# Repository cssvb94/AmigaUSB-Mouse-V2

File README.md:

# Amiga USB Mouse V2

USB to Amiga mouse interface using Arduino Pro Mini 3.3V and USB Host Shield Mini

USB Host Mini and Arduino Pro Mini mounting:

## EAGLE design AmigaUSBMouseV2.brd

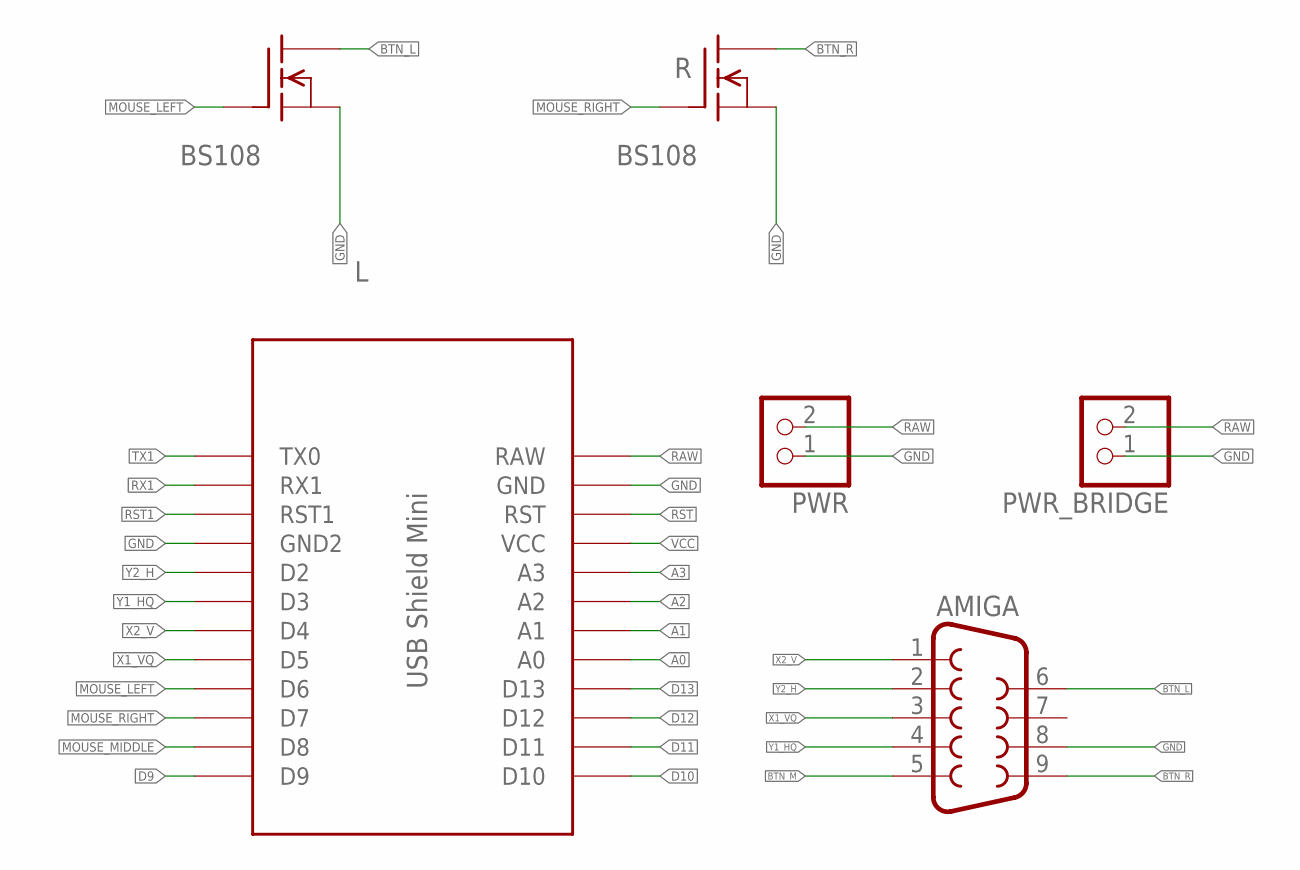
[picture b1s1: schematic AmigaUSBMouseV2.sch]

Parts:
AMIGA: F09D
L: BS108; TO92-INLINE
PWR: PINHD-1X2; 1X02
PWR_BRIDGE: PINHD-1X2; 1X02
R: BS108; TO92-INLINE
U$2: USB-SHIELD-MINI

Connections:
A0: U$2.A0
A1: U$2.A1
A2: U$2.A2
A3: U$2.A3
BTN_L: AMIGA.6, L.1 (D)
BTN_M: AMIGA.5
BTN_R: AMIGA.9, R.1 (D)
D9: U$2.D9
D10: U$2.D10
D11: U$2.D11
D12: U$2.D12
D13: U$2.D13
GND: AMIGA.8, L.3 (S), PWR.1, PWR_BRIDGE.1, R.3 (S), U$2.GND, U$2.GND1 (GND2)
MOUSE_LEFT: L.2 (G), U$2.D6
MOUSE_MIDDLE: U$2.D8
MOUSE_RIGHT: R.2 (G), U$2.D7
RAW: PWR.2, PWR_BRIDGE.2, U$2.RAW
RST: U$2.RST
RST1: U$2.RST1
RX1: U$2.RX1
TX1: U$2.TX0
VCC: U$2.VCC
X1_VQ: AMIGA.3, U$2.D5
X2_V: AMIGA.1, U$2.D4
Y1_HQ: AMIGA.4, U$2.D3
Y2_H: AMIGA.2, U$2.D2

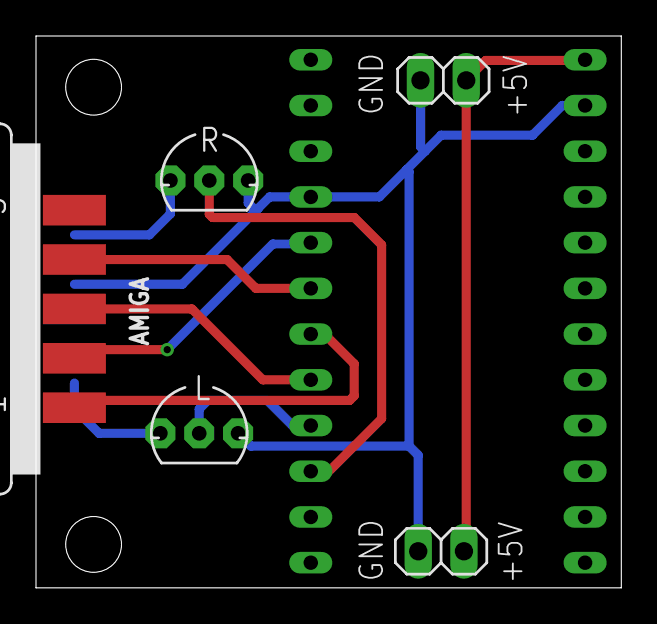
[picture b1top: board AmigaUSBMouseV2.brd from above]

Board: 2 copper layers, 32.5 x 30.7 mm, 6 parts (0 on the bottom side), 10 nets.

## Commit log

2018-09-18 Initial
2018-09-18 ReadMe
2018-09-19 PDFs and layout fixes
